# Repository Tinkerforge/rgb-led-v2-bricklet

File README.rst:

RGB LED Bricklet 2.0
====================

This repository contains the firmware source code and the hardware design
files. The documentation generator configs can be found at
https://github.com/Tinkerforge/generators

Repository Content
------------------

software/:
 * examples/: Examples for all supported languages
 * build/: Compiled files
 * src/: Source code of firmware
 * Makefile: Makefile to build project

hardware/:
 * Contains KiCad project files and additionally schematics as PDF

datasheets/:
 * Contains datasheets for sensors and complex ICs that are used

Hardware
--------

The hardware is designed with the open source EDA Suite KiCad
(http://www.kicad.org). Before you are able to open the files,
you have to install the Tinkerforge kicad-libraries
(https://github.com/Tinkerforge/kicad-libraries). You can either clone
them directly in hardware/ or clone them in a separate folder and
symlink them into hardware/
(ln -s kicad_path/kicad-libraries project_path/hardware). After that you
can open the .pro file in hardware/ with KiCad and from there view and
modify the schematics and the PCB layout.

Software
--------

If you want to do your own Brick/Bricklet firmware development we highly
recommend that you use our build environment setup script and read the
tutorial (https://www.tinkerforge.com/en/doc/Tutorials/Tutorial_Build_Environment/Tutorial.html).

To compile the C code we recommend you to install the newest GNU Arm Embedded
Toolchain (https://launchpad.net/gcc-arm-embedded/+download).
You also need to install bricklib2 (https://github.com/Tinkerforge/bricklib2).

You can either clone it directly in software/src/ or clone it in a
separate folder and symlink it into software/src/
(ln -s bricklib_path/bricklib2 project_path/software/src/). Finally make sure to
have CMake installed (http://www.cmake.org/cmake/resources/software.html).

After that you can build the firmware by invoking make in software/.
The firmware (.zbin) can then be found in software/build/ and uploaded
with brickv (click button "Flashing" on start screen).

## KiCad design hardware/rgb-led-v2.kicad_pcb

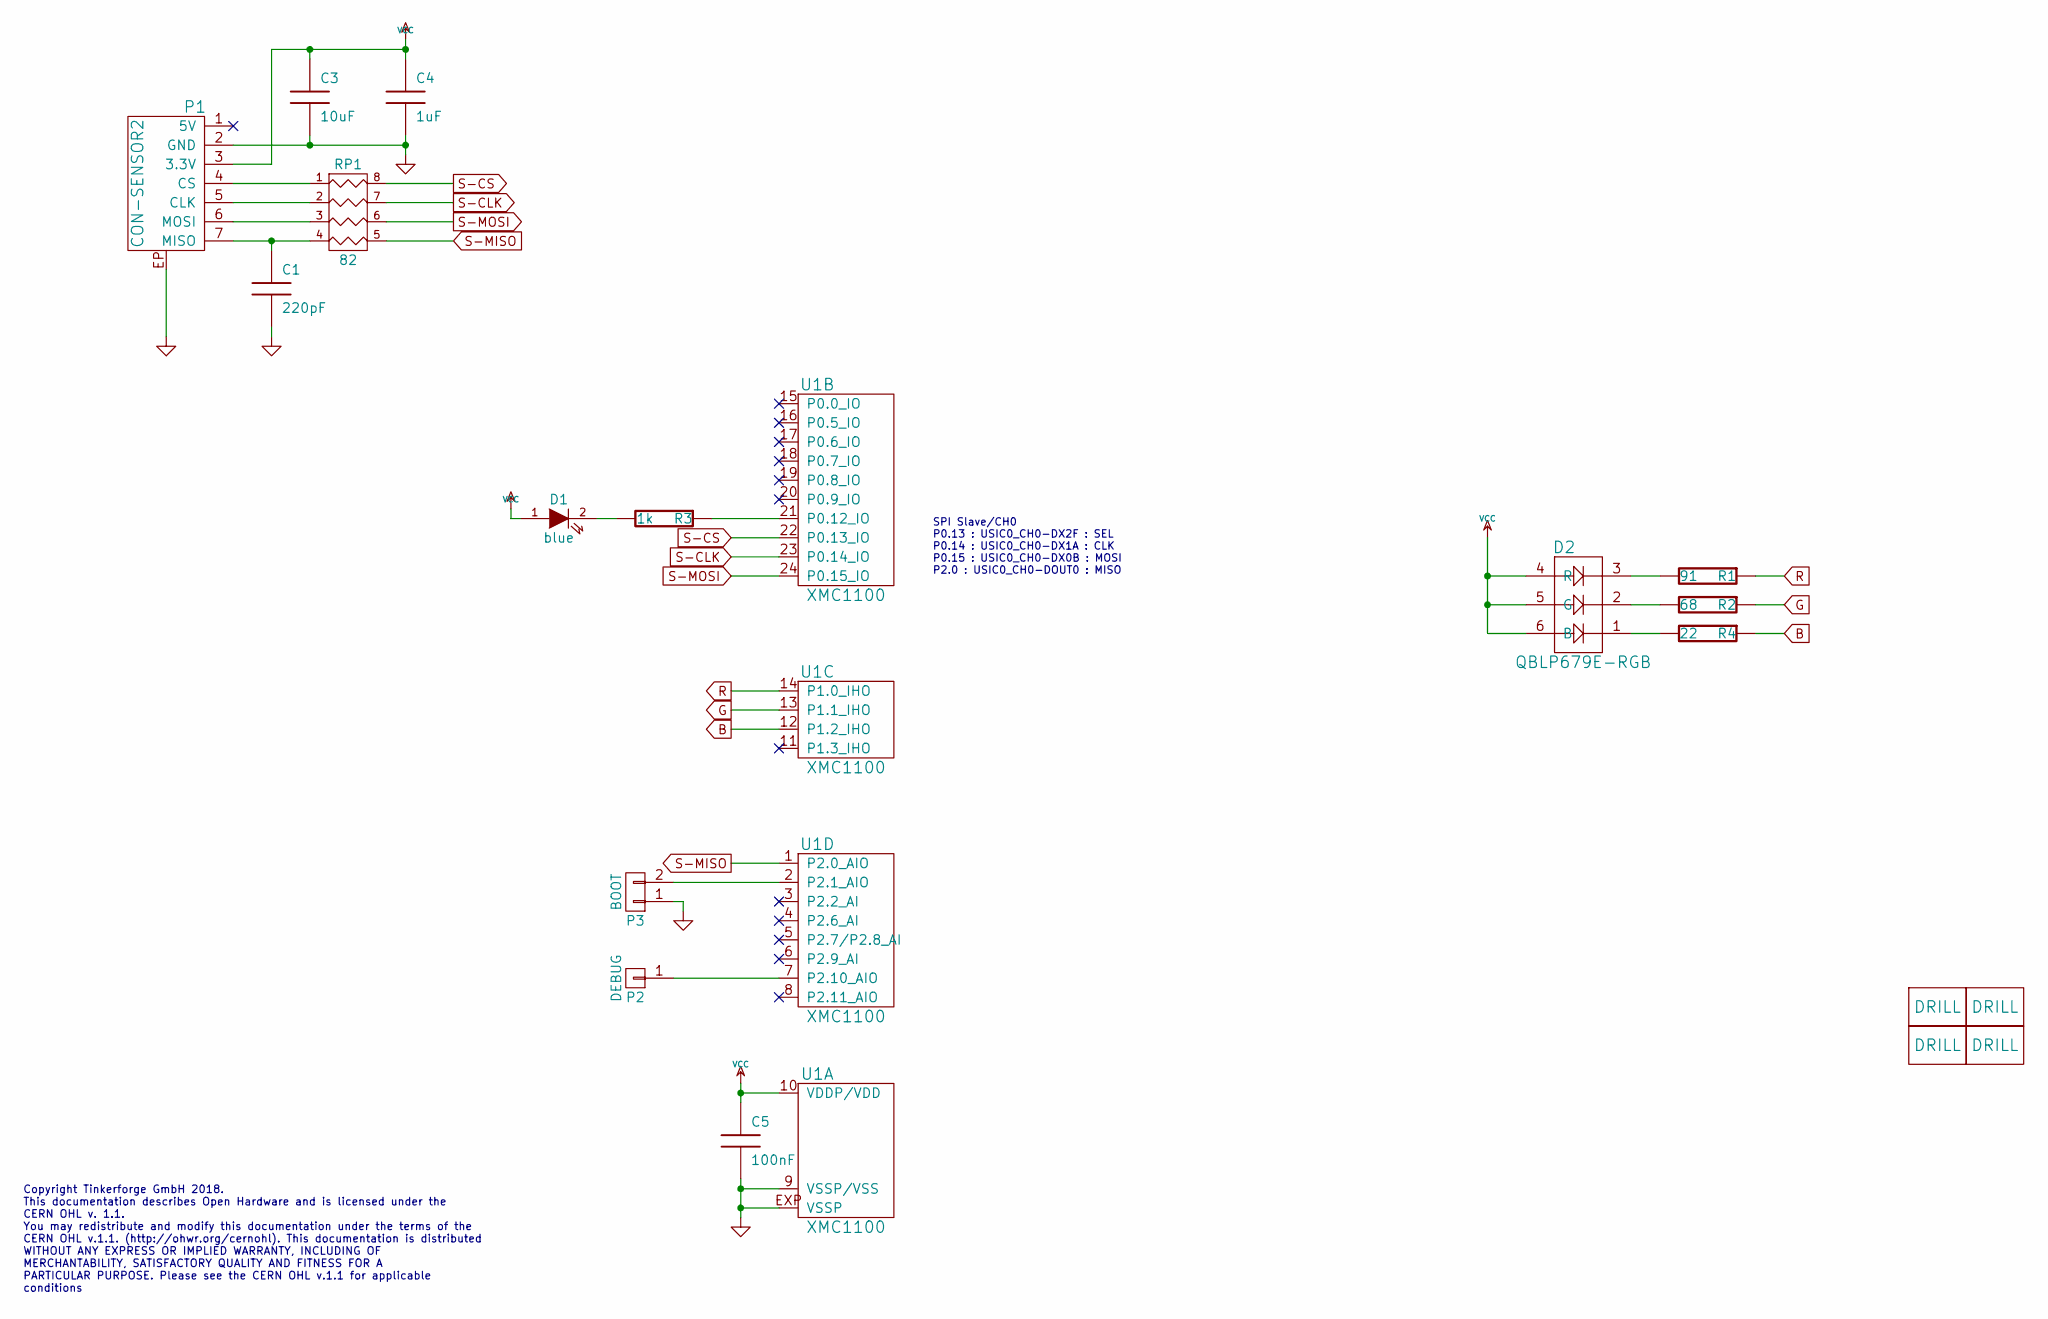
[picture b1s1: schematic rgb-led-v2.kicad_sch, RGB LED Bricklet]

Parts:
C1: 220pF; C0402F
C3: 10uF; C0805
C4: 1uF; C0603F
C5: 100nF; C0603F
D1: blue; D0603F
D2: QBLP679E-RGB; PLCC6-RGB
P1: CON-SENSOR2
P2: DEBUG; DEBUG_PAD
P3: BOOT; SolderJumper
R1: 91; R0603F
R2: 68; R0603F
R3: 1k; R0603F
R4: 22; R0603F
RP1: 82; 4X0402
U1: XMC1100; QFN24-4x4mm-0.5mm
U3, U4, U5, U6: DRILL; DRILL_NP

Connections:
B: R4.1, U1.12 (P1.2_IHO)
G: R2.1, U1.13 (P1.1_IHO)
GND: C1.2, C3.2, C4.2, C5.2, P1.2 (GND), P1.EP, P3.1, U1.9 (VSSP/VSS), U1.EXP (VSSP)
unnamed: C1.1, P1.7 (MISO), RP1.4
unnamed: D1.2 (K), R3.2
unnamed: D2.1, R4.2
unnamed: D2.2, R2.2
unnamed: D2.3, R1.2
unnamed: P1.4 (CS), RP1.1
unnamed: P1.5 (CLK), RP1.2
unnamed: P1.6 (MOSI), RP1.3
unnamed: P2.1, U1.7 (P2.10_AIO)
unnamed: P3.2, U1.2 (P2.1_AIO)
unnamed: R3.1, U1.21 (P0.12_IO)
R: R1.1, U1.14 (P1.0_IHO)
S-CLK: RP1.7 (R2), U1.23 (P0.14_IO)
S-CS: RP1.8 (R1), U1.22 (P0.13_IO)
S-MISO: RP1.5 (R4), U1.1 (P2.0_AIO)
S-MOSI: RP1.6 (R3), U1.24 (P0.15_IO)
VCC: C3.1, C4.1, C5.1, D1.1 (A), D2.4 (R), D2.5 (G), D2.6 (B), P1.3 (3.3V), U1.10 (VDDP/VDD)

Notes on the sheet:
Copyright Tinkerforge GmbH 2018. This documentation describes Open Hardware and is licensed under the CERN OHL v. 1.1. You may redistribute and modify this documentation under the terms of the CERN OHL v.1.1. (http://ohwr.org/cernohl). This documentation is distributed WITHOUT ANY EXPRESS OR IMPLIE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
SPI Slave/CH0 P0.13 : USIC0_CH0-DX2F : SEL P0.14 : USIC0_CH0-DX1A : CLK P0.15 : USIC0_CH0-DX0B : MOSI P2.0 : USIC0_CH0-DOUT0 : MISO

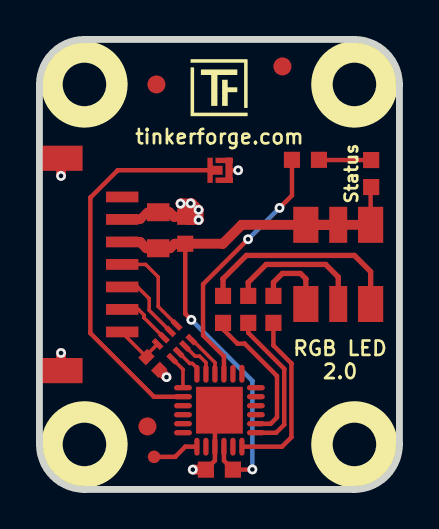
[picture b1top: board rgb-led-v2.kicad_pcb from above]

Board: 2 copper layers, 20.0 x 25.0 mm, 24 parts (2 on the bottom side), 20 nets.

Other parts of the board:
Fiducial_Mark: VAL**; Fiducial_Mark
Fiducial_Mark#2, Fiducial_Mark#3: VAL**; Fiducial_Mark
VAL: WEEE_7mm
VAL#2: CE_5mm

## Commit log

2018-06-27 Add schematic and layout
2018-06-28 Add .gitignore
2018-06-28 Fix readme
2018-07-11 Fix origin
2018-07-25 Add auto-generated stub firmware
2019-01-09 fix broken bottom layer, copper filled everything
2019-01-17 drc check
2019-01-18 update project settings
2019-01-29 fix schematic version, specify rgb led
2019-01-29 add kicad symbol table
2019-02-14 Add RGB LED API and driver implementation
2019-02-14 Add datasheet
2019-02-18 Add auto-generated examples
2019-02-22 changed procesor to XMC1100
2019-04-30 Turn logging off
2019-05-09 add schematic
2019-05-10 specify led position
2019-05-15 add 3d data
2019-05-20 Use bootloader fix in all new Bricklets
2019-05-20 Release Bricklet
2019-05-29 Increase version for new release (changes in bricklib2)
2019-05-29 Add rev to changelog
2020-01-13 examples: Use python3 input instead of python2 raw_input.
2020-03-16 Whitespace
2020-04-07 examples: rust: Always block when calling bindings functions.
2020-08-19 Add uc examples.
2020-08-25 uc: Fix whitespace
2020-08-27 uc: Fix warnings.
2020-09-02 uc: Add example driver note.
2021-10-25 Update KiCad link
    https://www.kicad.org/blog/2021/10/Avoid-links-to-former-kicad-domain/
2022-04-19 examples: uc: Rename TF_HalContext to TF_HAL.
2022-04-27 uc: Adapt to bindings changes
2022-07-06 Add license files.
2023-06-20 move to new kicad version

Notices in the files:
hardware/rgb-led-v2.kicad_pcb:
Licensed under CERN OHL v.1.1
Copyright (©) 2018, L.Lauer
